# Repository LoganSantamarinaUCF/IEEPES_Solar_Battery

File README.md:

# Solar-Powered Battery Pack ☀️🔋

Welcome to the hardware repository for the **IEEE PES UCF** Solar-Powered Battery Pack project! This repository contains all the KiCad schematic and PCB design files necessary for team collaboration.

---

## 📌 Project Overview

The goal of this project is to design and build a reliable, custom solar-powered battery pack. The system integrates solar energy harvesting, intelligent battery management, and efficient power conversion into a single cohesive hardware design.

### Key Features
* **Solar Panel Input:** Optimized power collection from external solar photovoltaic cells.
* **BQ Battery Management System (BMS):** Texas Instruments BQ-series IC implementation for safe charging, overvoltage/undervoltage protection, and thermal monitoring.
* **Custom Rectifier Circuit:** Designed for efficient power conditioning before reaching the charge controller.
* **Custom PCB:** Fully designed and layout-routed using KiCad.

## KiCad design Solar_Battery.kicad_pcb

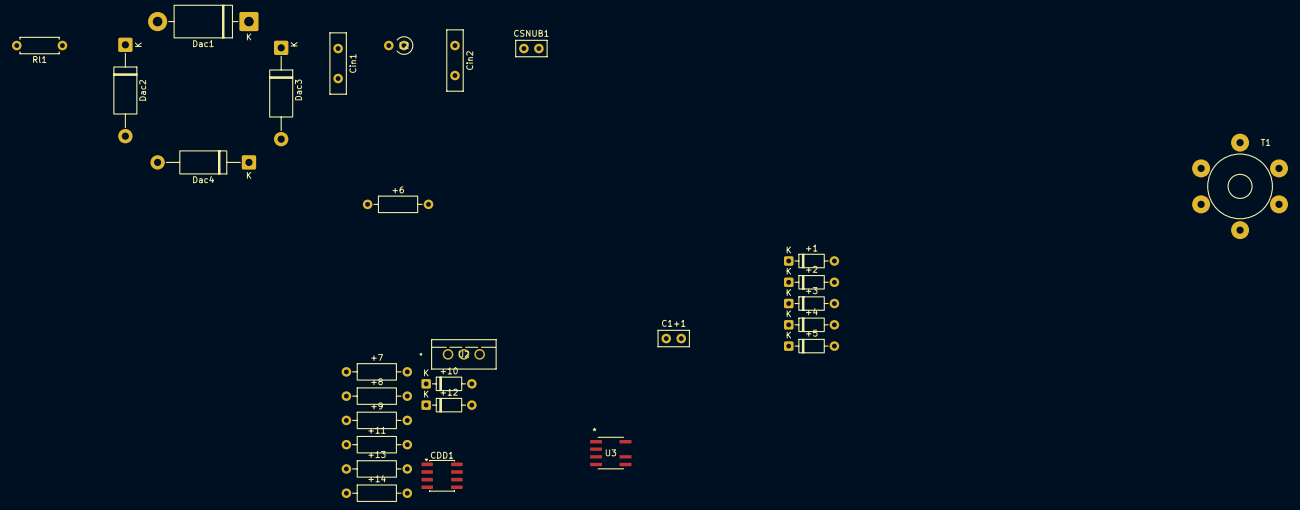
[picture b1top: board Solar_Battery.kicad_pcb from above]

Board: 2 copper layers, 28 parts (0 on the bottom side), 19 nets, no tracks yet.

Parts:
+1: RSNUB2; D_DO-35_SOD27_P7.62mm_Horizontal
+2: DSNUB; D_DO-35_SOD27_P7.62mm_Horizontal
+3: RSNUB1; D_DO-35_SOD27_P7.62mm_Horizontal
+4: D2-ZENER; D_DO-35_SOD27_P7.62mm_Horizontal
+5: RLBD; D_DO-35_SOD27_P7.62mm_Horizontal
+6: RG2; R_Axial_DIN0207_L6.3mm_D2.5mm_P10.16mm_Horizontal
+7: RG1; R_Axial_DIN0207_L6.3mm_D2.5mm_P10.16mm_Horizontal
+8: RLC; R_Axial_DIN0207_L6.3mm_D2.5mm_P10.16mm_Horizontal
+9: RCS; R_Axial_DIN0207_L6.3mm_D2.5mm_P10.16mm_Horizontal
+10: DZ-ZENER; D_DO-35_SOD27_P7.62mm_Horizontal
+11: RDD; R_Axial_DIN0207_L6.3mm_D2.5mm_P10.16mm_Horizontal
+12: D3-ZENER; D_DO-35_SOD27_P7.62mm_Horizontal
+13: RFBB; R_Axial_DIN0207_L6.3mm_D2.5mm_P10.16mm_Horizontal
+14: RFBT; R_Axial_DIN0207_L6.3mm_D2.5mm_P10.16mm_Horizontal
C1+1: C; C_Disc_D5.0mm_W2.5mm_P2.50mm
CDD1: +; SOIC-8_3.9x4.9mm_P1.27mm
CSNUB1: +; C_Disc_D5.0mm_W2.5mm_P2.50mm
Cin1, Cin2: 4.237uF; C_Disc_D10.0mm_W2.5mm_P5.00mm
Dac1: D; D_DO-201AD_P15.24mm_Horizontal
Dac2, Dac3, Dac4: D; D_DO-15_P15.24mm_Horizontal
L2: 470uH; L_Axial_L6.6mm_D2.7mm_P2.54mm_Vertical_Vishay_IM-2
Rl1: 13 ohm; R_Axial_DIN0207_L6.3mm_D2.5mm_P7.62mm_Horizontal
T1: T1; Transformer_Toroid_Tapped_Horizontal_D10.5mm_Amidon-T37
U2: IRF830APBF; TO220AB_VIS
U3: UCC28710DR; SO_UCC28710D_TEX

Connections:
/Rectifier/Diode_Bridge/Rectifier_Out: +3.1, CSNUB1.1, Cin2.1, L2.2, T1.3 (SA), U3.8 (HV)
/Rectifier/Diode_Bridge/Wall_Ground: Dac3.2 (A), Dac4.1 (K)
/Rectifier/Transformer_Output/Main_Output: +4.1 (K), +5.1, C1+1.1
/Rectifier/Transformer_Output/Mosfet_Snub: +2.2 (A), T1.4 (SB), U2.3 (D)
/Rectifier/Transformer_Output/Rectifier_GND: +5.2, C1+1.2, T1.1 (AA)
/Rectifier/Transformer_Output/Zener_UCC_Chip: +12.2 (A), +14.1, T1.6 (SD)
GND: +6.1, +9.2, +10.2 (A), +13.1, CDD1.2, Cin1.2, Cin2.2, Dac2.2 (A), Dac4.2 (A), T1.5 (SC), U3.4 (GND)
unnamed: +1.1, +3.2, CSNUB1.2
unnamed: +1.2, +2.1 (K)
unnamed: +4.2 (A), T1.2 (AB)
unnamed: +10.1 (K), +11.1, CDD1.1, U3.1 (VDD)
unnamed: +11.2, +12.1 (K)
unnamed: Dac1.2 (A), Dac2.1 (K), Rl1.1
unnamed: Cin1.1, Dac1.1 (K), Dac3.1 (K), L2.1
unnamed: +6.2, +7.1, U2.1 (G)
unnamed: +8.2, +9.1, U2.2 (S)
unnamed: +8.1, U3.5 (CS)
unnamed: +7.2, U3.6 (DRV)
unnamed: +13.2, +14.2, U3.2 (VS)
